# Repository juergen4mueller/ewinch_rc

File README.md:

# ewinch_remote_controller
 transmitter and receiver code for remote controlling a paragliding winch
 forked from robertzach/ewinch_remote_controller

receiver uses PPM for driving the winch and (optinal) UART to read additional information (line length, battery %, dutycycle)
VESC UART communication depends on https://github.com/SolidGeek/VescUart/

Line auto stop can be implemented within VESC with vesc_ppm_auto_stop.patch
Default VESC app config is vesc_app_config.xml

## Changes / Updates
 Changed ESP32-Board to custom made with MH-ET-ESP32-Devkit and Heltec ESP32-Lora(v3).
 chandrawi/LoRaRF-lib for usage of SX126x modul on Heltec v3.
 Made new case for Heltec module, same size but different mount points.
 Moved software project to PLATFORMIO using VSCode for convenience work.

## Software improvements:
 - rotary encoder in transmitter to adjust max. weight, default pull and transmitter id (push while switch on, then select and push to confirm)
 - EEPROM function in transmitter to hold last "max. weight" value.
 - rotary encoder in receiver used to pull manually (adjust force by turning, push stops immediately)

## work in progress
 - wind direction from winch transmitting to cockpit display
 - warning lamp if pull mode active
 - cutting system

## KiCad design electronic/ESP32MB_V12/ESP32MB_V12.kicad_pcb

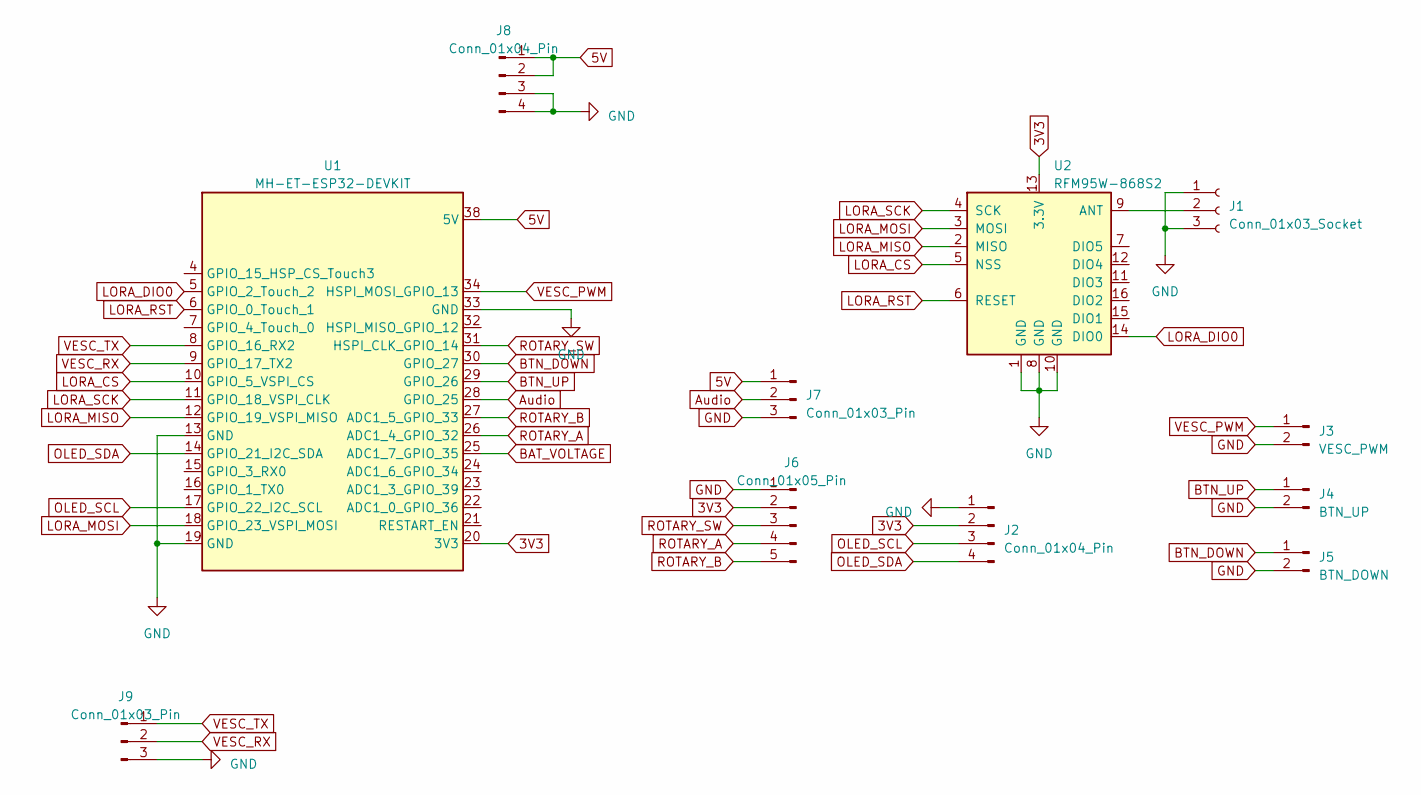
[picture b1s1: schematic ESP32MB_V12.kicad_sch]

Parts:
J1: Conn_01x03_Socket; PinHeader_1x03_P2.54mm_Vertical
J2: Conn_01x04_Pin; JST_PH_B4B-PH-K_1x04_P2.00mm_Vertical
J3: VESC_PWM; JST_PH_B2B-PH-K_1x02_P2.00mm_Vertical
J4: BTN_UP; JST_PH_B2B-PH-K_1x02_P2.00mm_Vertical
J5: BTN_DOWN; JST_PH_B2B-PH-K_1x02_P2.00mm_Vertical
J6: Conn_01x05_Pin; JST_PH_B5B-PH-K_1x05_P2.00mm_Vertical
J7, J9: Conn_01x03_Pin; JST_PH_B3B-PH-K_1x03_P2.00mm_Vertical
J8: Conn_01x04_Pin; PinHeader_1x04_P2.54mm_Vertical
U1: MH-ET-ESP32-DEVKIT; MH-ET-ESP32-Devkit
U2: RFM95W-868S2; HOPERF_RFM9XW_SMD

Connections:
3V3: J2.2, J6.2, U1.20 (3V3), U2.13 (3.3V)
5V: J7.1, J8.1, J8.2, U1.38 (5V)
Audio: J7.2, U1.28 (GPIO_25)
BAT_VOLTAGE: U1.25 (ADC1_7_GPIO_35)
BTN_DOWN: J5.1, U1.30 (GPIO_27)
BTN_UP: J4.1, U1.29 (GPIO_26)
GND: J1.1, J1.3, J2.1, J3.2, J4.2, J5.2, J6.1, J7.3, J8.3, J8.4, J9.3, U1.13 (GND), U1.19 (GND), U1.33 (GND), U2.1 (GND), U2.8 (GND), U2.10 (GND)
LORA_CS: U1.10 (GPIO_5_VSPI_CS), U2.5 (NSS)
LORA_DIO0: U1.5 (GPIO_2_Touch_2), U2.14 (DIO0)
LORA_MISO: U1.12 (GPIO_19_VSPI_MISO), U2.2 (MISO)
LORA_MOSI: U1.18 (GPIO_23_VSPI_MOSI), U2.3 (MOSI)
LORA_RST: U1.6 (GPIO_0_Touch_1), U2.6 (RESET)
LORA_SCK: U1.11 (GPIO_18_VSPI_CLK), U2.4 (SCK)
unnamed: J1.2, U2.9 (ANT)
OLED_SCL: J2.3, U1.17 (GPIO_22_I2C_SCL)
OLED_SDA: J2.4, U1.14 (GPIO_21_I2C_SDA)
ROTARY_A: J6.4, U1.26 (ADC1_4_GPIO_32)
ROTARY_B: J6.5, U1.27 (ADC1_5_GPIO_33)
ROTARY_SW: J6.3, U1.31 (HSPI_CLK_GPIO_14)
VESC_PWM: J3.1, U1.34 (HSPI_MOSI_GPIO_13)
VESC_RX: J9.2, U1.9 (GPIO_17_TX2)
VESC_TX: J9.1, U1.8 (GPIO_16_RX2)

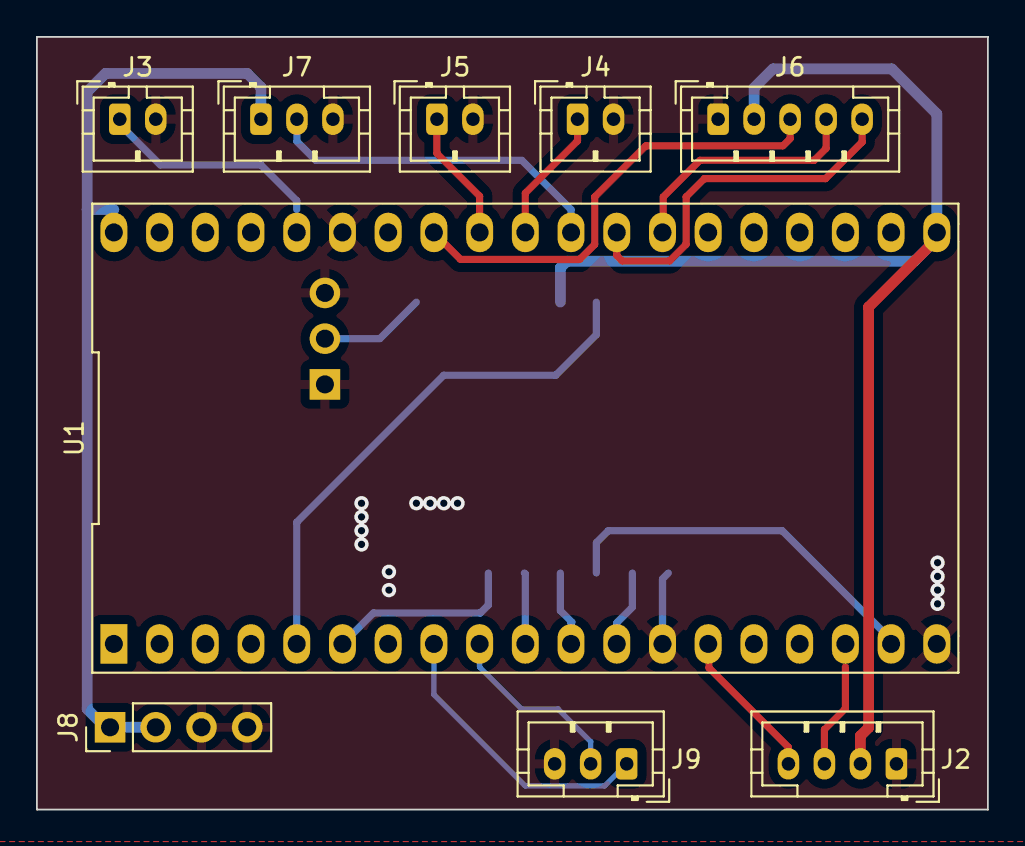
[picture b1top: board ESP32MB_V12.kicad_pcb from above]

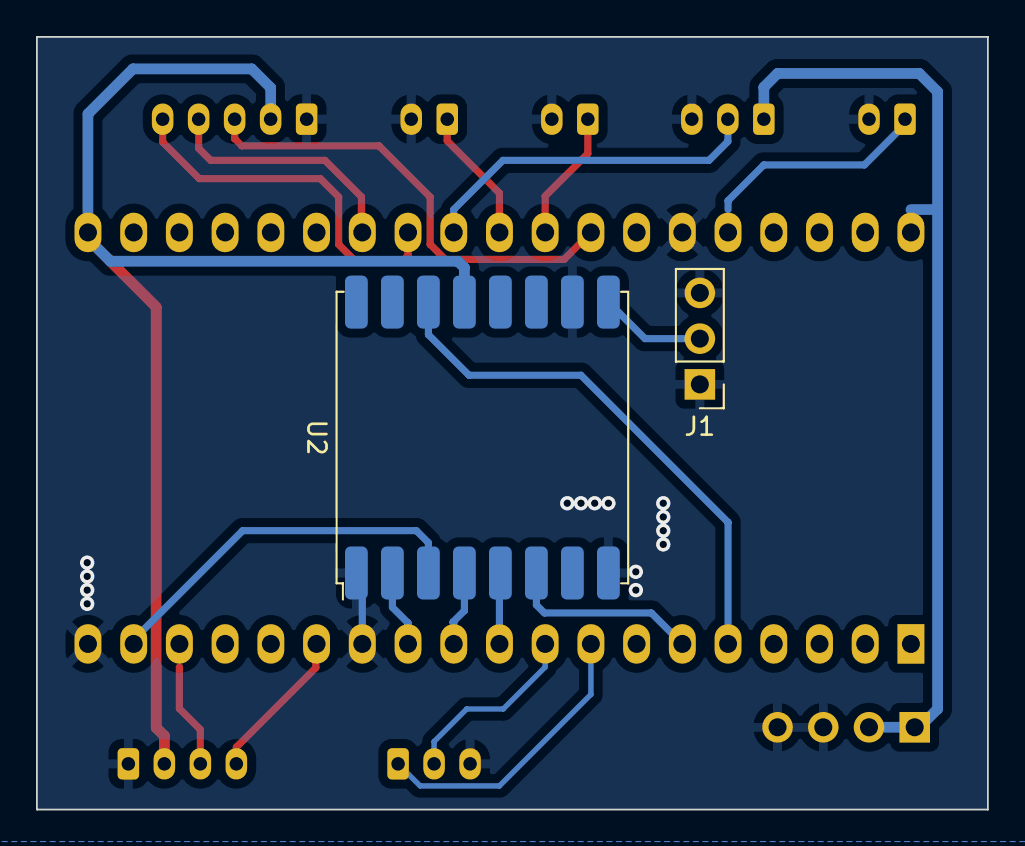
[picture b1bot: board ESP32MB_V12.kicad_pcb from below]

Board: 2 copper layers, 52.8 x 42.9 mm, 11 parts (2 on the bottom side), 21 nets.

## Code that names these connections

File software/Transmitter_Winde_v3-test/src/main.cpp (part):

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
  #define LED_ONBOARD 35
  // Setup Lora neu
  #define LORA_SCK      9    // GPIO5  -- SX1278's SCK
  #define LORA_MISO    11   // GPIO19 -- SX1278's MISnO
  #define LORA_MOSI    10   // GPIO27 -- SX1278's MOSI
  #define LORA_SS       8   // GPIO18 -- SX1278's CS
  #define LORA_RST     12   // GPIO14 -- SX1278's RESET
  #define LORA_BUSY    13  // only on Heltec Module connected
  #define LORA_DI0     14   // GPIO26 -- SX1278's IRQ(Interrupt Request)

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    }
  }
  // Pins Rotary Encoder
  #define ROTARY_SW  2
  #define ROTARY_A   3
  #define ROTARY_B   4

  // Buttons for state machine control
  #define BUTTON_UP    5 // up
  #define BUTTON_DOWN  6 // down

  // Pins OLED Display
  #define OLED_SDA  17
  #define OLED_SCL  18
  #define OLED_RST  21 // only in Heltec mode used

  #define BAT_AN_IN  1
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}

void encoderInit(void){
  pinMode(ROTARY_A, INPUT_PULLUP);
  pinMode(ROTARY_B, INPUT_PULLUP);
  attachInterrupt(ROTARY_A, rotaryInterrupt, CHANGE);
  attachInterrupt(ROTARY_B, rotaryInterrupt, CHANGE);
}
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  display.flipScreenVertically();  
  Serial.println("Init Display");
  // Pin-Definition Rotary
  pinMode(ROTARY_SW, INPUT_PULLUP);
  encoderInit();

  Serial.println("Init EEPROM");
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
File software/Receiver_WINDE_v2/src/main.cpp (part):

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
//   // // Pins Rotary Encoder

//   // #define ROTARY_SW  2
//   // #define ROTARY_A   3
//   // #define ROTARY_B   4

//   // // Buttons for state machine control
//   // #define BUTTON_UP    5 // up
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
//   // Pins OLED Display

  #define OLED_SDA  4
  #define OLED_SCL  15
  #define OLED_RST  16 // only in Heltec mode used

  // No battery used in receiver
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  //Battery Voltage IO 7 -> Wind direction
  // #define WindInAnalog  7

  #define VESC_RX  22    //connect to TX on Vesc
  #define VESC_TX  23    //connect to RX on Vesc

  // #define Cutter_Out 40 // up
  // #define LED_RT 41 // down
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
//Using VescUart librarie to read from Vesc (https://github.com/SolidGeek/VescUart/)
// Uart old
// #define VESC_RX  14    //connect to TX on Vesc
// #define VESC_TX  2    //connect to RX on Vesc
// Uart new

VescUart vescUART;
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}

void encoderInit(void){
  // pinMode(ROTARY_A, INPUT_PULLUP);
  // pinMode(ROTARY_B, INPUT_PULLUP);
  // attachInterrupt(ROTARY_A, rotaryInterrupt, CHANGE);
  // attachInterrupt(ROTARY_B, rotaryInterrupt, CHANGE);
}
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
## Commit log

2023-12-26 prepared for line cutter
2024-02-22 Firmware FOC G300 mit Autostop hinzu
2024-06-03 Added CockpitDisplay to project
2024-06-03 modified Transmitter SW for Cockpit Display
2024-06-03 sorted vesc folder
2024-06-03 cleaned old sw
2024-06-03 addad gitignore
2024-06-18 Changed Lora to 866.5 MHz and set SF to 9, changed RadioLib receiver to interrupt
2024-06-18 changed Receiver SW to work with 886.5 MHz and SF9
2024-07-21 added wind direction sensor to receiver
2024-07-21 Added wind direction to cockpit display
2024-07-21 updated vesc config
2024-09-04 some improvements and cad data addad
2025-02-22 added gitignore
2025-03-18 added pictures
2026-02-27 Update Transmitter_v3 mit powerManager zum Laden
2026-03-06 Transmitter und Receiver auf Heltec Lora v3 angepasst. Lora stabil mit Interrupt, Reichweite rund 1,3km. 400ms Cycle läuft. Anpassung der restlichen SW steht noch aus
2026-03-07 Transmitter code working after redesign
2026-03-09 Receiver fully working after adjusting interrupt behaviour
2026-03-09 IRQ error handling extented
2026-03-09 IRQ handling extented
